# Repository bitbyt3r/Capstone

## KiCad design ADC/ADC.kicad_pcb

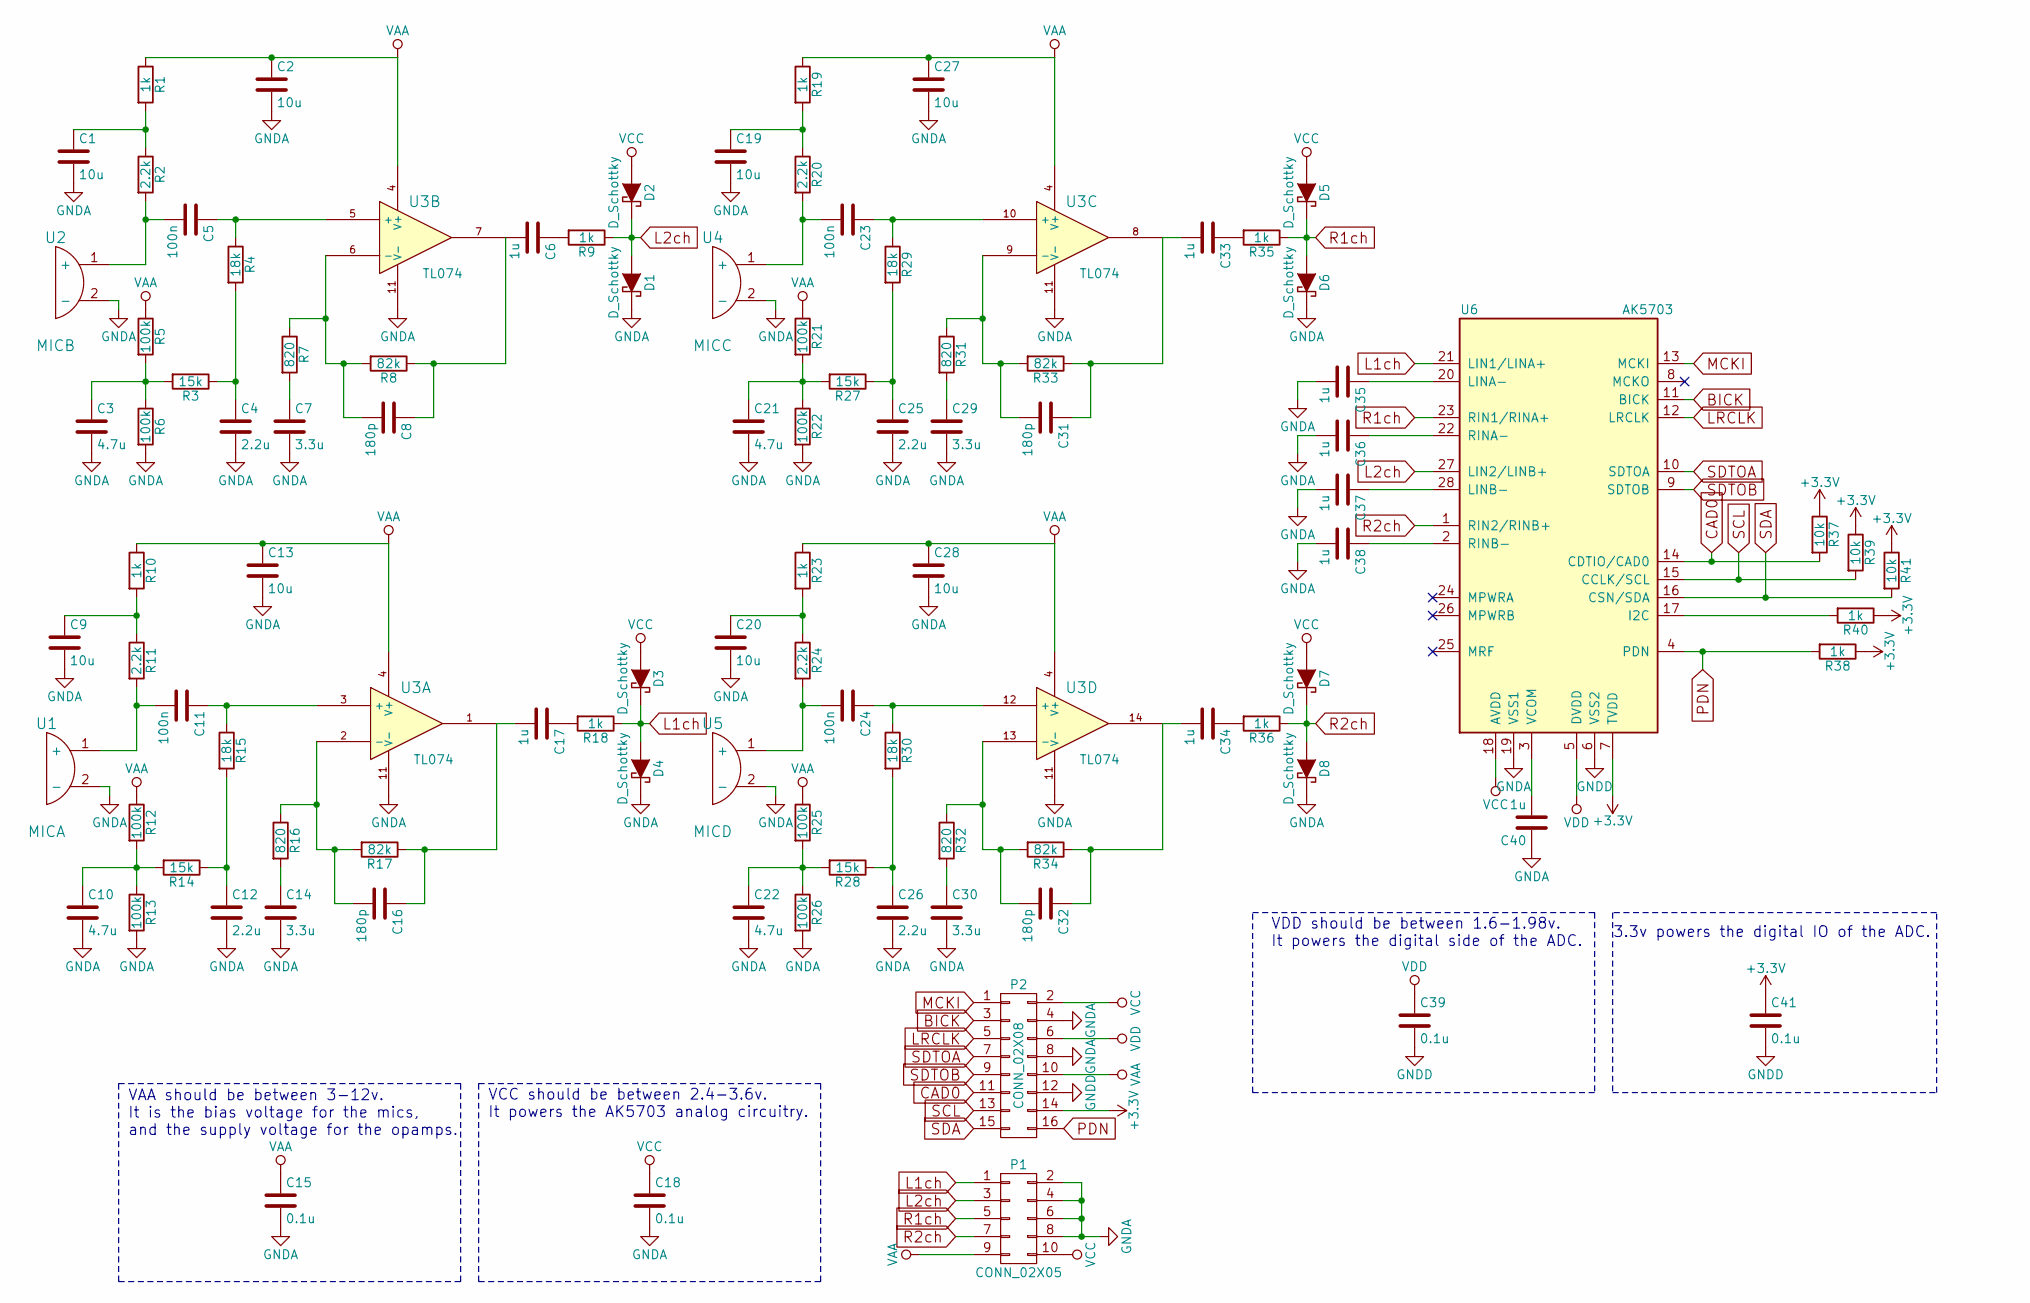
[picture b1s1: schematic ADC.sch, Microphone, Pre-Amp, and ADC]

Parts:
C1, C2, C9, C13, C19, C20, C27, C28: 10u; C_0603_HandSoldering
C3, C10, C21, C22: 4.7u; C_0603_HandSoldering
C4, C12, C25, C26: 2.2u; C_0603_HandSoldering
C5, C11, C23, C24: 100n; C_0603_HandSoldering
C6, C17, C33, C34, C35, C36, C37, C38, C40: 1u; C_0603_HandSoldering
C7, C14, C29, C30: 3.3u; C_0603_HandSoldering
C8, C16, C31, C32: 180p; C_0603_HandSoldering
C15, C18, C39, C41: 0.1u; C_0603_HandSoldering
D1, D2, D3, D4, D5, D6, D7, D8: D_Schottky; Diode_DO-41_SOD81_Horizontal_RM10
P1: CONN_02X05; Pin_Header_Straight_2x05
P2: CONN_02X08; Pin_Header_Straight_2x08
R1, R9, R10, R18, R19, R23, R35, R36, R38, R40: 1k; R_0603_HandSoldering
R2, R11, R20, R24: 2.2k; R_0603_HandSoldering
R3, R14, R27, R28: 15k; R_0603_HandSoldering
R4, R15, R29, R30: 18k; R_0603_HandSoldering
R5, R6, R12, R13, R21, R22, R25, R26: 100k; R_0603_HandSoldering
R7, R16, R31, R32: 820; R_0603_HandSoldering
R8, R17, R33, R34: 82k; R_0603_HandSoldering
R37, R39, R41: 10k; R_0603_HandSoldering
U1: MICA; MagneticBuzzer_Kingstate_KCG0601
U2: MICB; MagneticBuzzer_Kingstate_KCG0601
U3: TL074; TSSOP-14_4.4x5mm_Pitch0.65mm
U4: MICC; MagneticBuzzer_Kingstate_KCG0601
U5: MICD; MagneticBuzzer_Kingstate_KCG0601
U6: AK5703; QFN-28-1EP_4x4mm_Pitch0.4mm

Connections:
+3V3: C41.1, P2.14, R37.1, R38.1, R39.1, R40.1, R41.1, U6.7 (TVDD)
BICK: P2.3, U6.11 (BICK)
CAD0: P2.11, R37.2, U6.14 (CDTIO/CAD0)
GNDA: C1.2, C2.2, C3.2, C4.2, C7.2, C9.2, C10.2, C12.2, C13.2, C14.2, C15.2, C18.2, C19.2, C20.2, C21.2, C22.2, C25.2, C26.2, C27.2, C28.2, C29.2, C30.2, C35.2, C36.2, C37.2, C38.2, C40.1, D1.2 (K), D4.2 (K), D6.2 (K), D8.2 (K), P1.2, P1.4, P1.6, P1.8, P2.4, P2.8, R6.2, R13.2, R22.2, R26.2, U1.2 (-), U2.2 (-), U3.11 (V-), U4.2 (-), U5.2 (-), U6.19 (VSS1)
GNDD: C39.2, C41.2, P2.12, U6.6 (VSS2)
L1ch: D3.2 (K), D4.1 (A), P1.1, R18.1, U6.21 (LIN1/LINA+)
L2ch: D1.1 (A), D2.2 (K), P1.3, R9.1, U6.27 (LIN2/LINB+)
LRCLK: P2.5, U6.12 (LRCLK)
MCKI: P2.1, U6.13 (MCKI)
unnamed: C1.1, R1.2, R2.1
unnamed: C3.1, R3.2, R5.2, R6.1
unnamed: C4.1, R3.1, R4.2
unnamed: C5.1, R4.1, U3.5 (+)
unnamed: C5.2, R2.2, U2.1 (+)
unnamed: C6.1, R9.2
unnamed: C6.2, C8.1, R8.1, U3.7
unnamed: C7.1, R7.2
unnamed: C8.2, R7.1, R8.2, U3.6 (-)
unnamed: C9.1, R10.2, R11.1
unnamed: C10.1, R12.2, R13.1, R14.2
unnamed: C11.1, R15.1, U3.3 (+)
unnamed: C11.2, R11.2, U1.1 (+)
unnamed: C12.1, R14.1, R15.2
unnamed: C14.1, R16.2
unnamed: C16.1, C17.2, R17.1, U3.1
unnamed: C16.2, R16.1, R17.2, U3.2 (-)
unnamed: C17.1, R18.2
unnamed: C19.1, R19.2, R20.1
unnamed: C20.1, R23.2, R24.1
unnamed: C21.1, R21.2, R22.1, R27.2
unnamed: C22.1, R25.2, R26.1, R28.2
unnamed: C23.1, R29.1, U3.10 (+)
unnamed: C23.2, R20.2, U4.1 (+)
unnamed: C24.1, R30.1, U3.12 (+)
unnamed: C24.2, R24.2, U5.1 (+)
unnamed: C25.1, R27.1, R29.2
unnamed: C26.1, R28.1, R30.2
unnamed: C29.1, R31.2
unnamed: C30.1, R32.2
unnamed: C31.1, C33.2, R33.1, U3.8
unnamed: C31.2, R31.1, R33.2, U3.9 (-)
unnamed: C32.1, C34.2, R34.1, U3.14
unnamed: C32.2, R32.1, R34.2, U3.13 (-)
unnamed: C33.1, R35.2
unnamed: C34.1, R36.2
unnamed: C35.1, U6.20 (LINA-)
unnamed: C36.1, U6.22 (RINA-)
unnamed: C37.1, U6.28 (LINB-)
unnamed: C38.1, U6.2 (RINB-)
unnamed: C40.2, U6.3 (VCOM)
unnamed: R40.2, U6.17 (I2C)
PDN: P2.16, R38.2, U6.4 (PDN)
R1ch: D5.2 (K), D6.1 (A), P1.5, R35.1, U6.23 (RIN1/RINA+)
R2ch: D7.2 (K), D8.1 (A), P1.7, R36.1, U6.1 (RIN2/RINB+)
SCL: P2.13, R39.2, U6.15 (CCLK/SCL)
SDA: P2.15, R41.2, U6.16 (CSN/SDA)
SDTOA: P2.7, U6.10 (SDTOA)
SDTOB: P2.9, U6.9 (SDTOB)
VAA: C2.1, C13.1, C15.1, C27.1, C28.1, P1.9, P2.10, R1.1, R5.1, R10.1, R12.1, R19.1, R21.1, R23.1, R25.1, U3.4 (V+)
VCC: C18.1, D2.1 (A), D3.1 (A), D5.1 (A), D7.1 (A), P1.10, P2.2, U6.18 (AVDD)
VDD: C39.1, P2.6, U6.5 (DVDD)

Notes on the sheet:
VAA should be between 3-12v. It is the bias voltage for the mics, and the supply voltage for the opamps.
VCC should be between 2.4-3.6v. It powers the AK5703 analog circuitry.
VDD should be between 1.6-1.98v. It powers the digital side of the ADC.
3.3v powers the digital IO of the ADC.

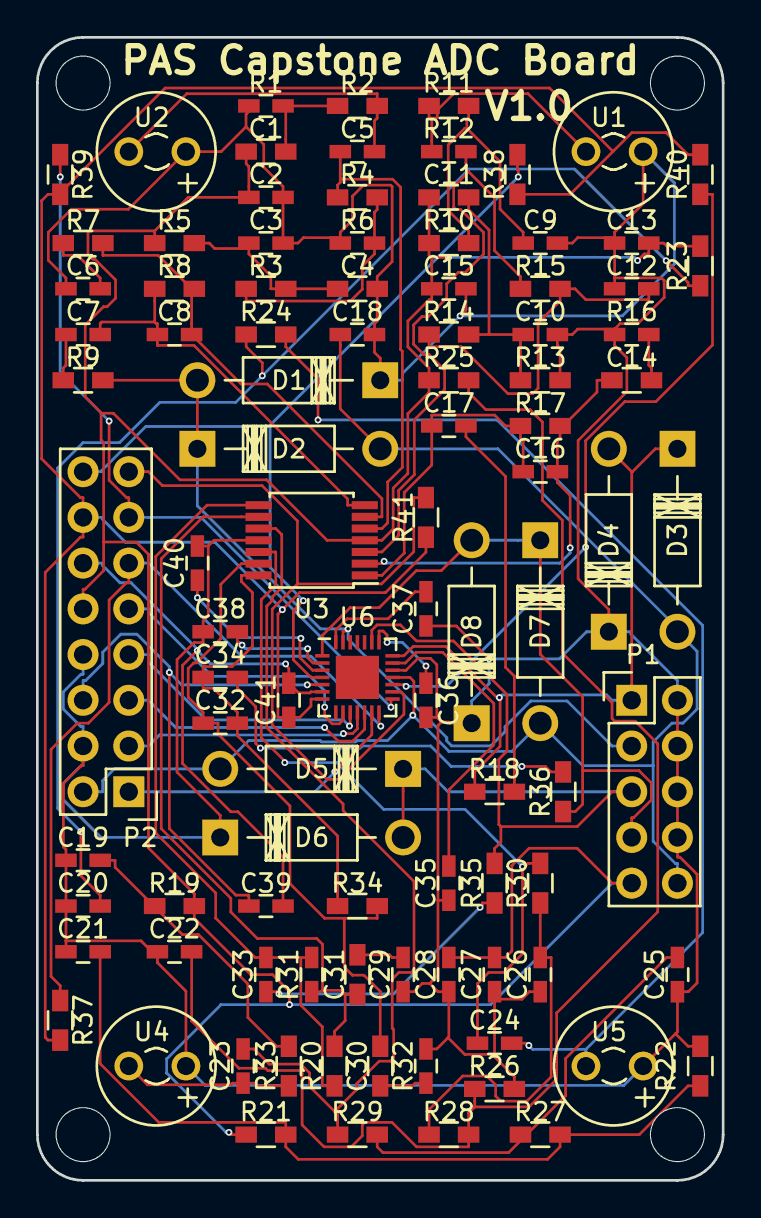
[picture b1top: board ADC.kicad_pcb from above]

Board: 2 copper layers, 38.1 x 63.5 mm, 98 parts (0 on the bottom side), 61 nets.

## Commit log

2015-11-09 Added base project for ADC board
2015-11-09 Added schematic symbol for AK5703
2015-11-09 Analog side complete
2015-11-09 Finished Digital Section
2015-11-09 Schematic complete, need footprint for mic
2015-11-09 Saved Project
2015-11-16 Added freeroute and the first pass at a PCB
2015-11-16 Expanded board, all files
2015-11-16 Updated project
2015-11-16 Added plot files
2015-11-16 Added plot1
2015-11-16 Should be ready for production now.
2015-11-18 Adjusted 3d models
2015-11-30 Added 3d model
2015-12-07 Updated project files
2015-12-07 matlab files
2015-12-10 added software to do beam steering
    arrayAquisition aquires NI and data, and kicks off scan
    steering, computes delays in seconds,
    Make_Delay shifts input channels based on steering
2015-12-14 Scans for the date 12/13/15
    added scans
2015-12-14 an explanation of the csv files.
    this is the code used for the csv, but with comments so you can see
    which data cooresponds to which csv files
2016-02-17 filter code rough draft
    just my thoughts so far
2016-02-17 filter matlab code
    scratchfilt i wrote to implement polynomial math. using as template for
    filter verilog module
2016-03-18 added new code
2016-03-21 Added arraygui
2016-05-06 Added processing files
2016-05-06 Added scanning code
2016-05-06 Added array code
2016-05-06 Added dataserver
